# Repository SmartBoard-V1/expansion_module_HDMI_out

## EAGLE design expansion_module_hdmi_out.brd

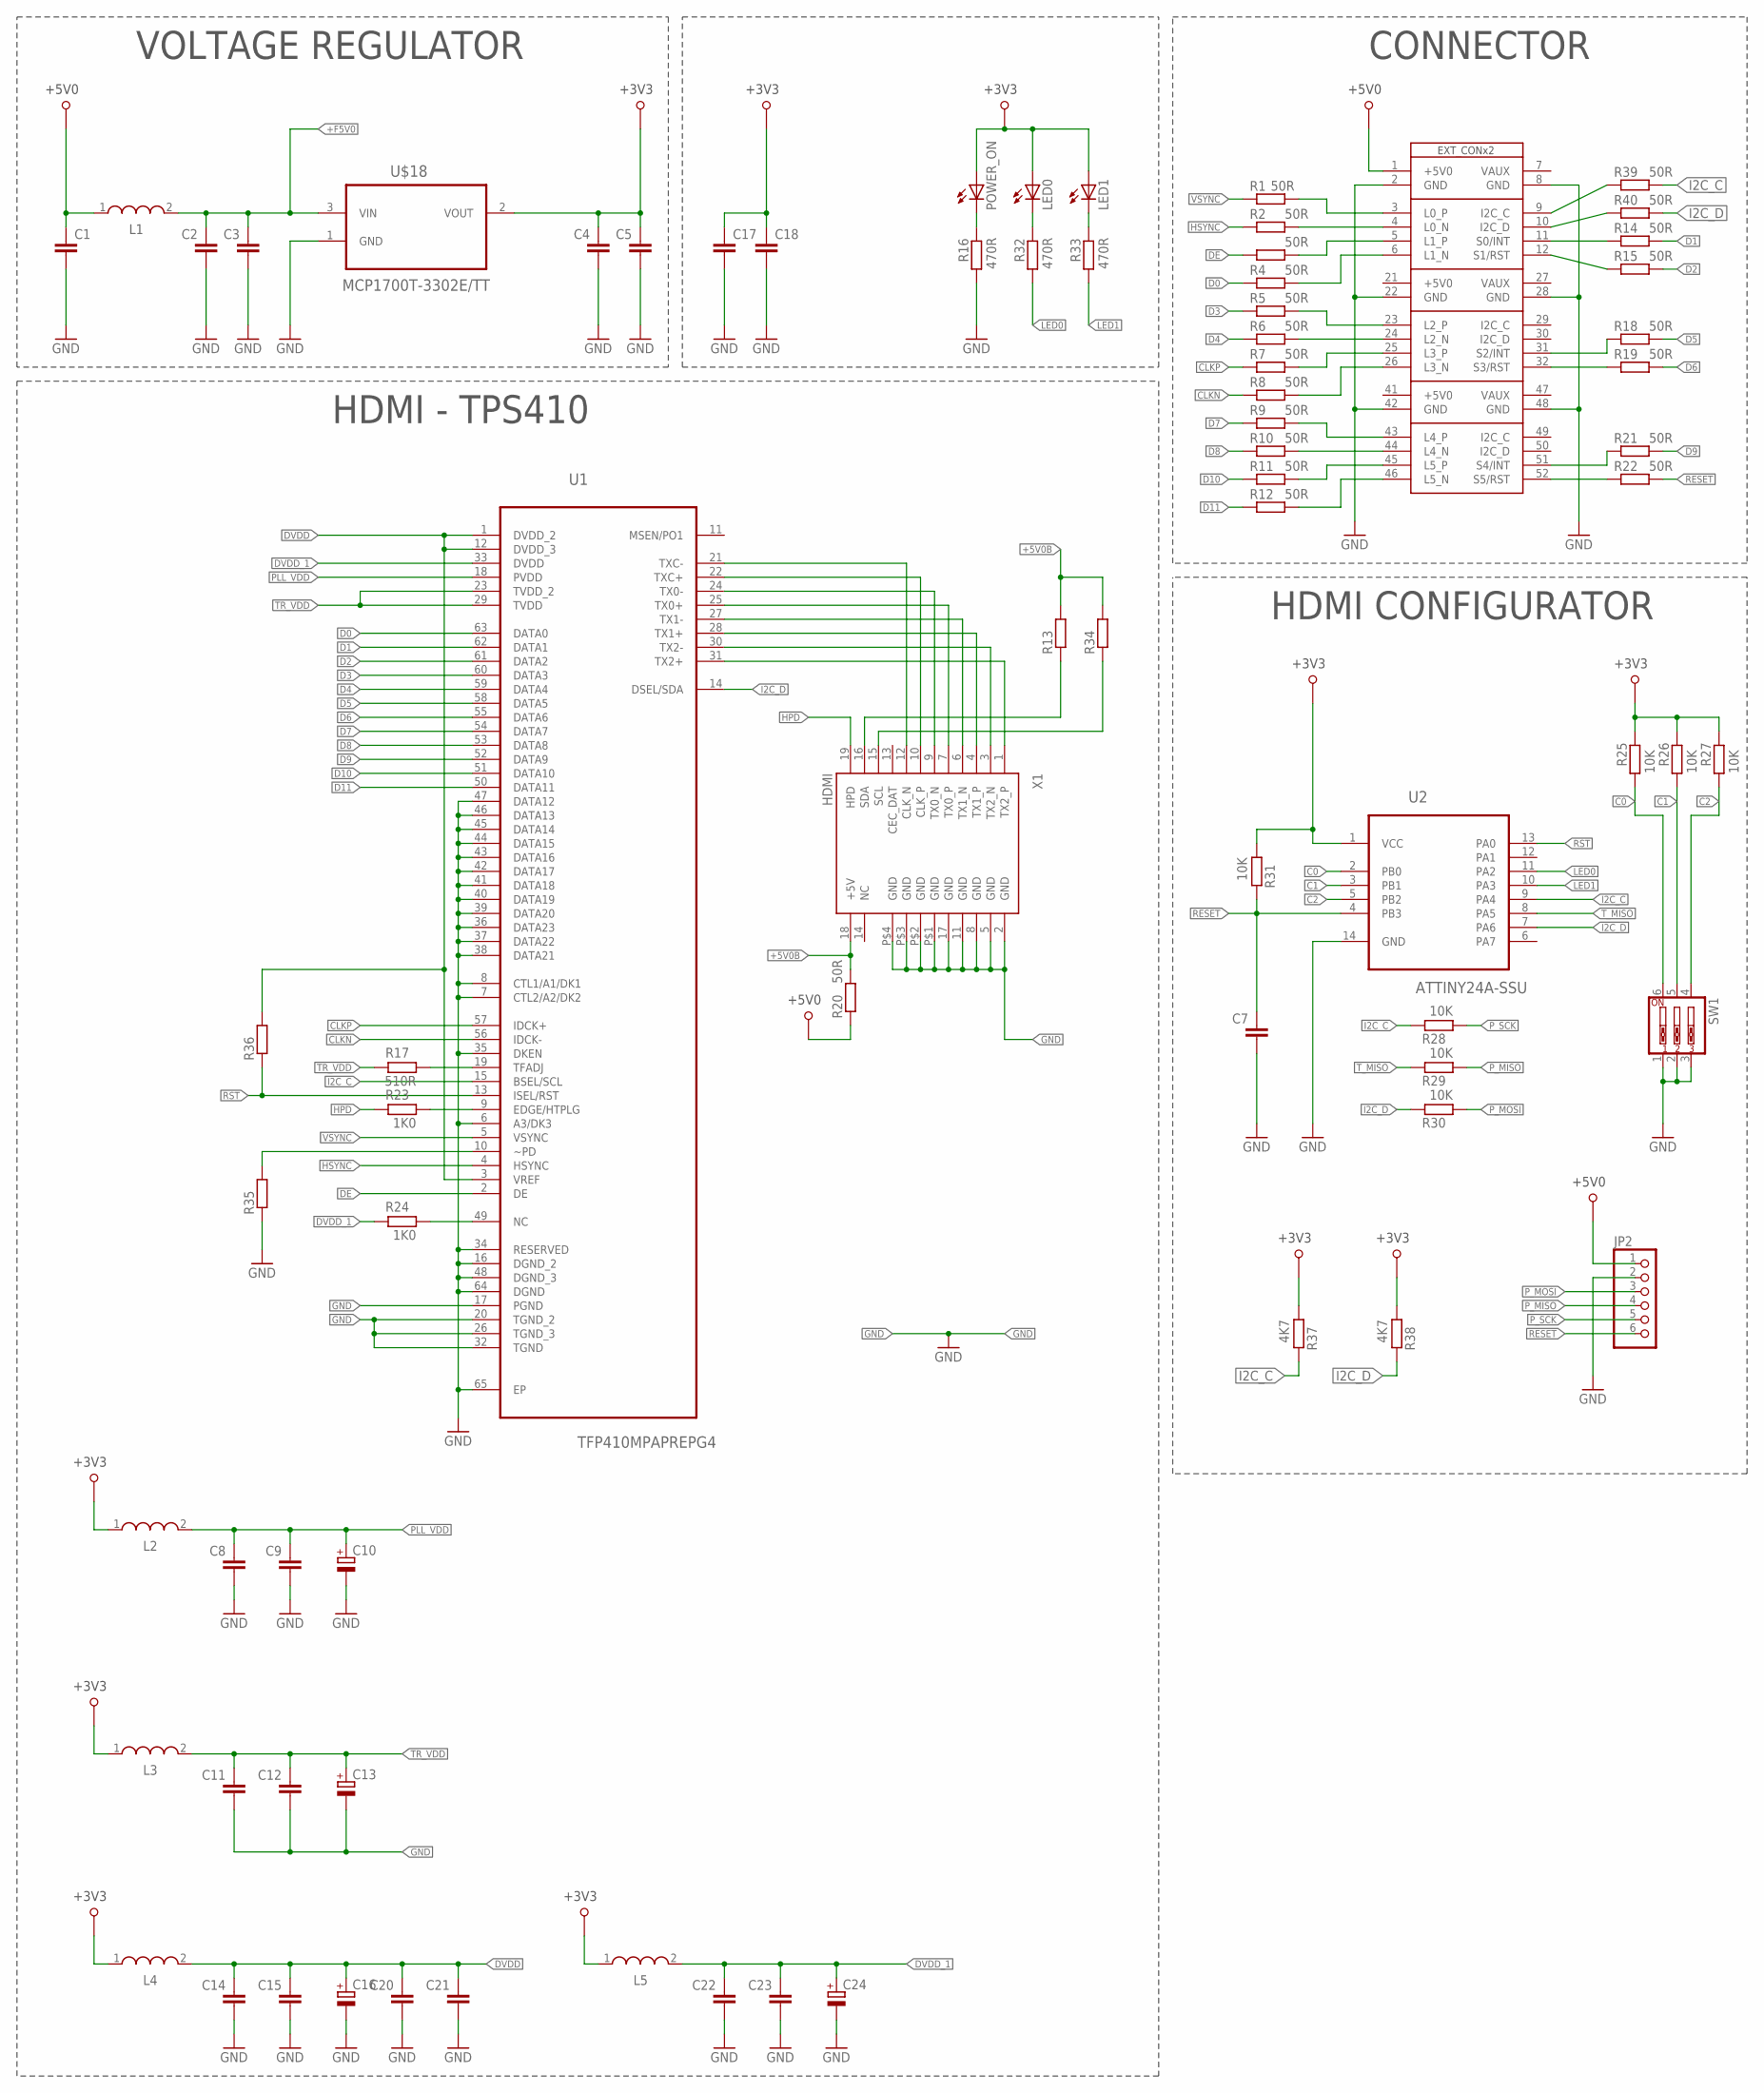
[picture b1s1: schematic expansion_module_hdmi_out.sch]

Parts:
C1, C17, C18: C-EUC1210K; C1210K
C2, C3, C4, C5, C7, C8, C9, C11, C12, C14, C15, C20, C21, C22, C23: C-EUC0805; C0805
C10, C13, C16, C24: CPOL-EUSMCB; SMC_B
JP2: PINHD-1X6; 1X06
L1, L2, L3, L4, L5: WE-LQ_1210; WE-LQ_M
LED0, LED1: LEDCHIPLED_0805; CHIPLED_0805
POWER_ON: LEDCHIPLED_0805; CHIPLED_0805
R1, R2, R3, R4, R5, R6, R7, R8, R9, R10, R11, R12, R14, R15, R18, R19, R20, R21, R22, R39, R40: 50R; R0805
R13, R34, R35, R36: R-EU_R0603; R0603
R16, R32, R33: 470R; R0805
R17: 510R; R0805
R23, R24: 1K0; R0805
R25, R26, R27, R28, R29, R30, R31: 10K; R0805
R37, R38: 4K7; R0805
SW1: SW_DIP-3; EDG-03
U1: TFP410MPAPREPG4; QFP50P1200X1200X120-65N
U2: ATTINY24A-SSU; SOIC127P600X175-14N
U$1: SB_EXT_CON_X3; SB_EXT_CON_X3_FULL
U$18: MCP1700T-3302E/TT; SOT95P237X112-3N
X1: HDMI

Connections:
+3V3: C4.2, C5.2, C17.1, C18.1, L2.1, L3.1, L4.1, L5.1, LED0.A, LED1.A, POWER_ON.A, R25.2, R26.2, R27.2, R31.1, R37.1, R38.1, U2.1 (VCC), U$18.2 (VOUT)
+5V0: C1.1, JP2.1, L1.1, R20.1, U$1.1 (+5V0)
+5V0B: R13.2, R20.2, R34.2, X1.18 (+5V)
+F5V0: C2.2, C3.2, L1.2, U$18.3 (VIN)
C0: R25.1, SW1.6, U2.2 (PB0)
C1: R26.1, SW1.5, U2.3 (PB1)
C2: R27.1, SW1.4, U2.5 (PB2)
CLKN: R8.1, U1.56 (IDCK-)
CLKP: R7.1, U1.57 (IDCK+)
D0: R4.1, U1.63 (DATA0)
D1: R14.2, U1.62 (DATA1)
D2: R15.2, U1.61 (DATA2)
D3: R5.1, U1.60 (DATA3)
D4: R6.1, U1.59 (DATA4)
D5: R18.2, U1.58 (DATA5)
D6: R19.2, U1.55 (DATA6)
D7: R9.1, U1.54 (DATA7)
D8: R10.1, U1.53 (DATA8)
D9: R21.2, U1.52 (DATA9)
D10: R11.1, U1.51 (DATA10)
D11: R12.1, U1.50 (DATA11)
DE: R3.1, U1.2 (DE)
DVDD: C14.2, C15.2, C16.+, C20.2, C21.2, L4.2, R36.2, U1.1 (DVDD_2), U1.3 (VREF), U1.12 (DVDD_3)
DVDD_1: C22.2, C23.2, C24.+, L5.2, R24.2, U1.33 (DVDD)
GND: C1.2, C2.1, C3.1, C4.1, C5.1, C7.1, C8.1, C9.1, C10.-, C11.1, C12.1, C13.-, C14.1, C15.1, C16.-, C17.2, C18.2, C20.1, C21.1, C22.1, C23.1, C24.-, JP2.2, R16.1, R35.1, SW1.1, SW1.2, SW1.3, U1.6 (A3/DK3), U1.7 (CTL2/A2/DK2), U1.8 (CTL1/A1/DK1), U1.16 (DGND_2), U1.17 (PGND), U1.20 (TGND_2), U1.26 (TGND_3), U1.32 (TGND), U1.34 (RESERVED), U1.35 (DKEN), U1.36 (DATA23), U1.37 (DATA22), U1.38 (DATA21), U1.39 (DATA20), U1.40 (DATA19), U1.41 (DATA18), U1.42 (DATA17), U1.43 (DATA16), U1.44 (DATA15), U1.45 (DATA14), U1.46 (DATA13), U1.47 (DATA12), U1.48 (DGND_3), U1.64 (DGND), U1.65 (EP), U2.14 (GND), U$1.2 (GND), U$1.8 (GND), U$1.22 (GND), U$1.28 (GND), U$1.42 (GND), U$1.48 (GND), U$18.1 (GND), X1.2 (GND), X1.5 (GND), X1.8 (GND), X1.11 (GND), X1.17 (GND), X1.P$1 (GND), X1.P$2 (GND), X1.P$3 (GND), X1.P$4 (GND)
HPD: R23.2, X1.19 (HPD)
HSYNC: R2.1, U1.4 (HSYNC)
I2C_C: R28.2, R37.2, R39.2, U1.15 (BSEL/SCL), U2.9 (PA4)
I2C_D: R30.2, R38.2, R40.2, U1.14 (DSEL/SDA), U2.7 (PA6)
LED0: R32.1, U2.11 (PA2)
LED1: R33.1, U2.10 (PA3)
unnamed: R1.2, U$1.3 (L0_P)
unnamed: R2.2, U$1.4 (L0_N)
unnamed: R3.2, U$1.5 (L1_P)
unnamed: R4.2, U$1.6 (L1_N)
unnamed: R5.2, U$1.23 (L2_P)
unnamed: R15.1, U$1.12 (S1/RST)
unnamed: R14.1, U$1.11 (S0/INT)
unnamed: LED0.C, R32.2
unnamed: R18.1, U$1.31 (S2/INT)
unnamed: R6.2, U$1.24 (L2_N)
unnamed: R17.1, U1.19 (TFADJ)
unnamed: R7.2, U$1.25 (L3_P)
unnamed: R8.2, U$1.26 (L3_N)
unnamed: R9.2, U$1.43 (L4_P)
unnamed: R10.2, U$1.44 (L4_N)
unnamed: R11.2, U$1.45 (L5_P)
unnamed: R19.1, U$1.32 (S3/RST)
unnamed: R34.1, X1.15 (SCL)
unnamed: R21.1, U$1.51 (S4/INT)
unnamed: R22.1, U$1.52 (S5/RST)
unnamed: POWER_ON.C, R16.2
unnamed: U1.31 (TX2+), X1.1 (TX2_P)
unnamed: U1.30 (TX2-), X1.3 (TX2_N)
unnamed: U1.28 (TX1+), X1.4 (TX1_P)
unnamed: U1.27 (TX1-), X1.6 (TX1_N)
unnamed: U1.25 (TX0+), X1.7 (TX0_P)
unnamed: U1.24 (TX0-), X1.9 (TX0_N)
unnamed: U1.22 (TXC+), X1.10 (CLK_P)
unnamed: R12.2, U$1.46 (L5_N)
unnamed: U1.21 (TXC-), X1.12 (CLK_N)
unnamed: R35.2, U1.10 (~PD)
unnamed: R24.1, U1.49 (NC)
unnamed: R23.1, U1.9 (EDGE/HTPLG)
unnamed: LED1.C, R33.2
unnamed: R13.1, X1.16 (SDA)
unnamed: R40.1, U$1.10 (I2C_D)
unnamed: R39.1, U$1.9 (I2C_C)
PLL_VDD: C8.2, C9.2, C10.+, L2.2, U1.18 (PVDD)
P_MISO: JP2.4, R29.1
P_MOSI: JP2.3, R30.1
P_SCK: JP2.5, R28.1
RESET: C7.2, JP2.6, R22.2, R31.2, U2.4 (PB3)
RST: R36.1, U1.13 (ISEL/RST), U2.13 (PA0)
TR_VDD: C11.2, C12.2, C13.+, L3.2, R17.2, U1.23 (TVDD_2), U1.29 (TVDD)
T_MISO: R29.2, U2.8 (PA5)
VSYNC: R1.1, U1.5 (VSYNC)

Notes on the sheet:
CONNECTOR
VOLTAGE REGULATOR
HDMI - TPS410
HDMI CONFIGURATOR

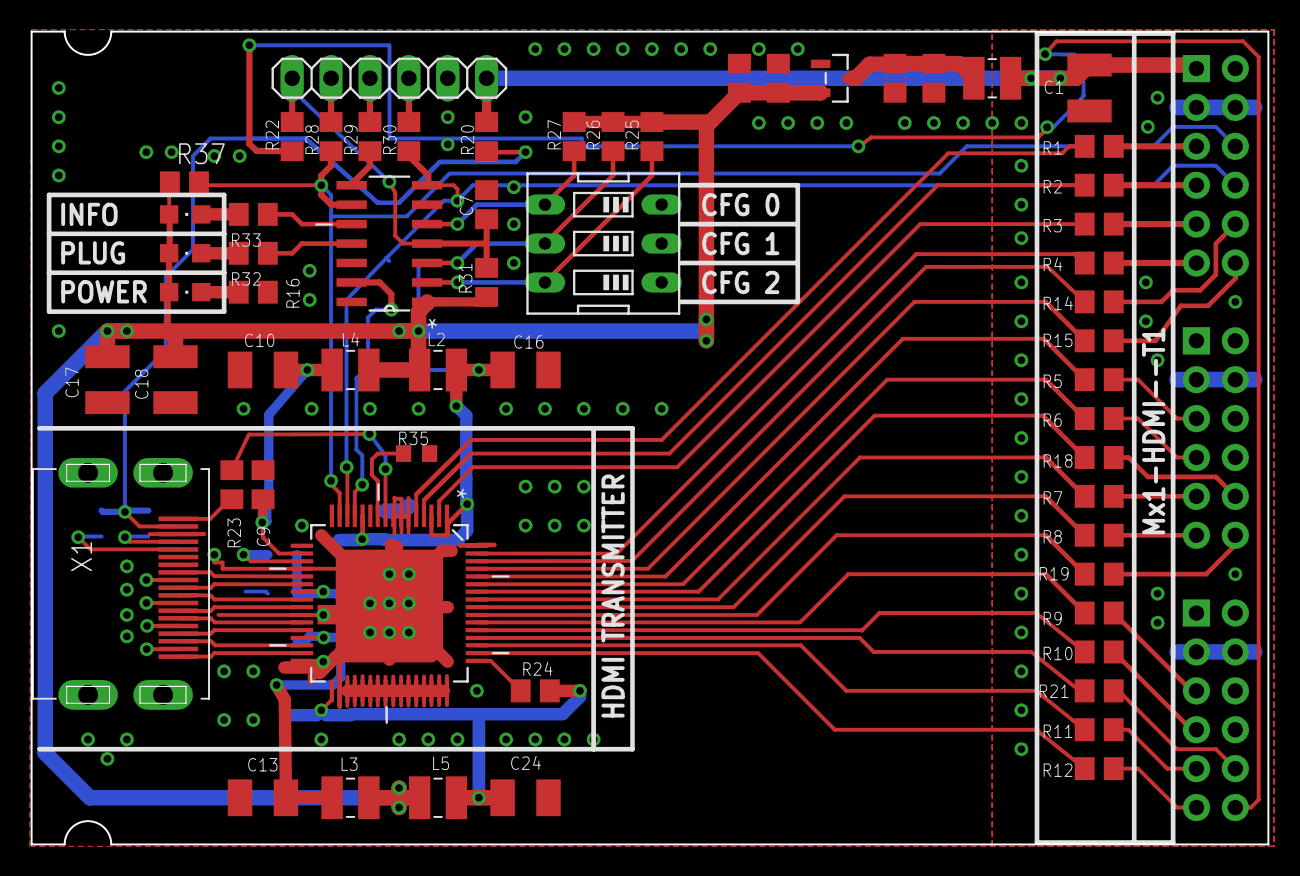
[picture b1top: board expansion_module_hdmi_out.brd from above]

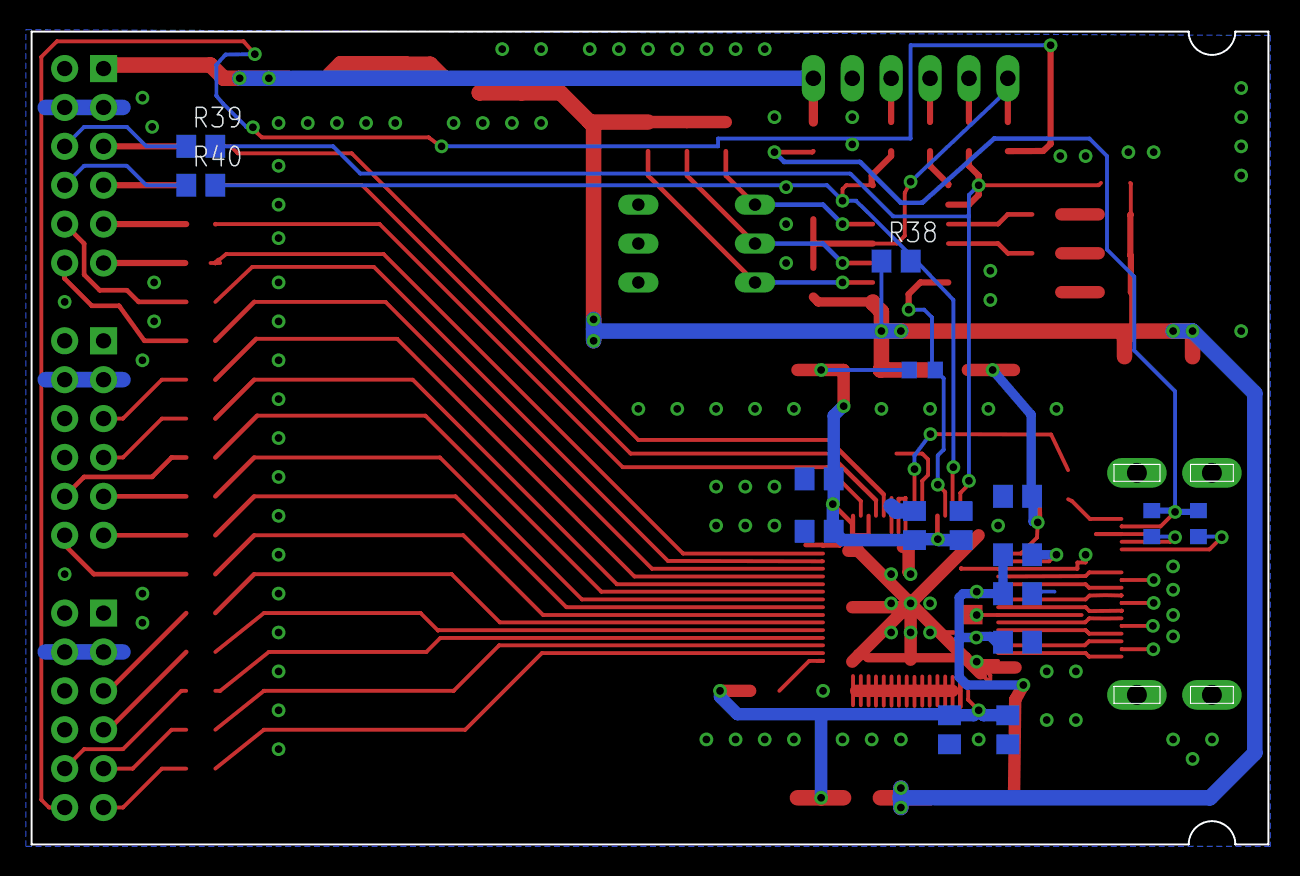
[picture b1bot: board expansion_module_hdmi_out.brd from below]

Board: 2 copper layers, 80.8 x 53.1 mm, 77 parts (16 on the bottom side), 77 nets.

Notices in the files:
parts and their libraries:
EagleLibrary_Wuerth_Elektronik_eiSos_rev: Copyright: Würth Elektronik
